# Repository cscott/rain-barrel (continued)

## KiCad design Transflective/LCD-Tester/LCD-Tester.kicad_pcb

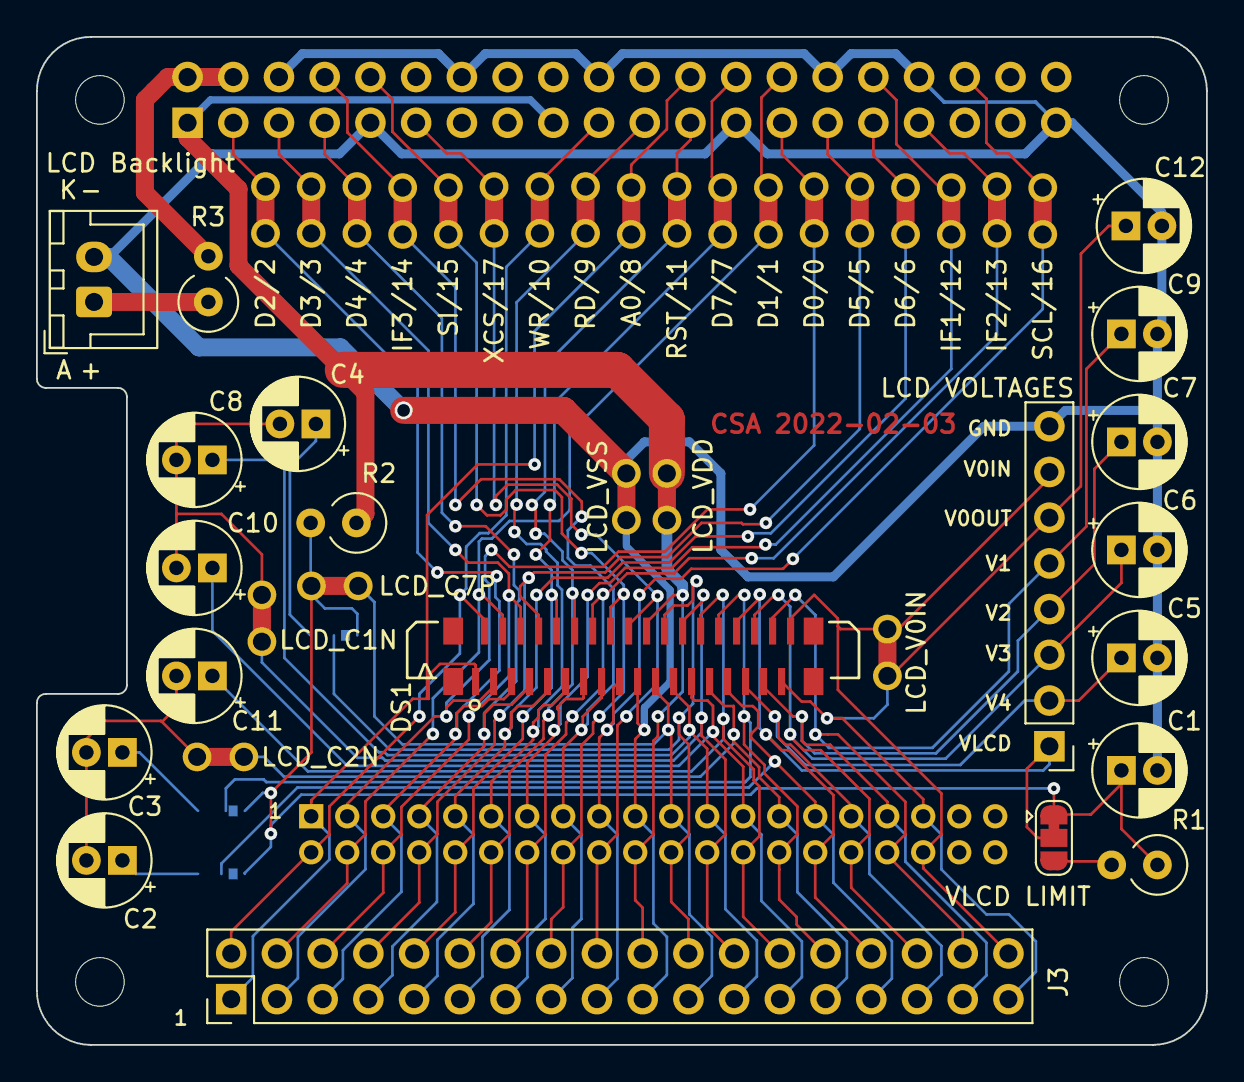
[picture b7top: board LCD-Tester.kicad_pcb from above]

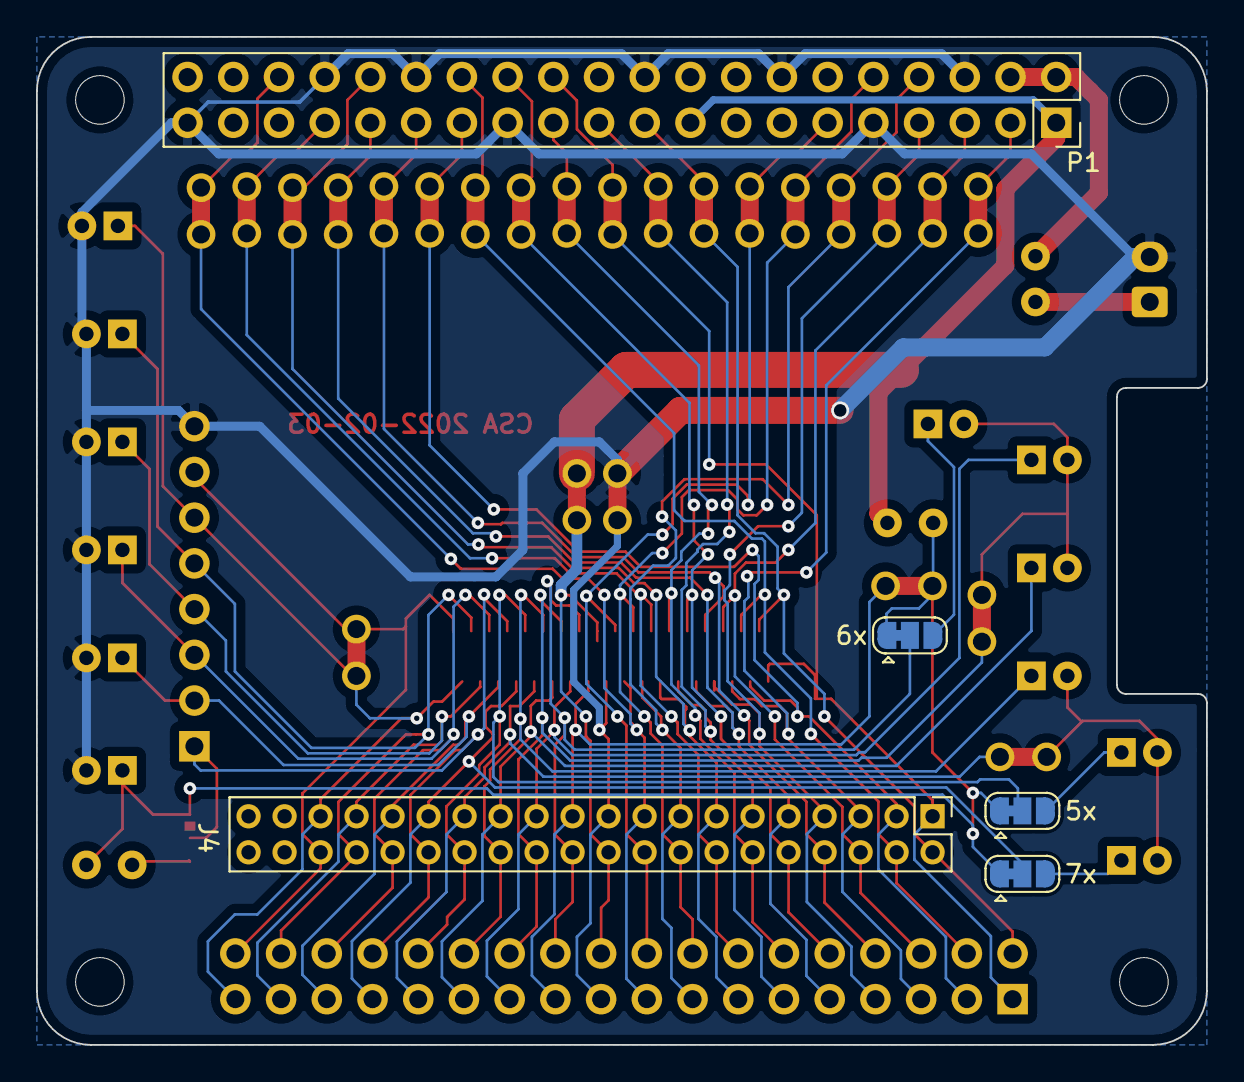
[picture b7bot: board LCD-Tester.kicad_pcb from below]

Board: 2 copper layers, 65.0 x 56.0 mm, 53 parts (5 on the bottom side), 65 nets.

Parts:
C1, C2, C3, C4, C5, C6, C7, C8, C9, C10, C11, C12: 1uF; CP_Radial_D5.0mm_P2.00mm
DS1: DISPLAYTECH-128240D; F314-1A7H1-11036
J1: LCD VOLTAGES; PinHeader_1x08_P2.54mm_Vertical
J2: LCD Backlight; JST_XH_B2B-XH-A_1x02_P2.50mm_Vertical
J3: Conn_01x36_Male; PinHeader_2x18_P2.54mm_Vertical
J4: Conn_01x36_Male; PinHeader_2x20_P2.00mm_Vertical
JP1: D2/2; Jumper-THT-NC
JP2: D3/3; Jumper-THT-NC
JP3: D4/4; Jumper-THT-NC
JP4: XCS/17; Jumper-THT-NC
JP5: WR/10; Jumper-THT-NC
JP6: RD/9; Jumper-THT-NC
JP7: RST/11; Jumper-THT-NC
JP8: D0/0; Jumper-THT-NC
JP9: D5/5; Jumper-THT-NC
JP10: D6/6; Jumper-THT-NC
JP11: IF2/13; Jumper-THT-NC
JP12: IF3/14; Jumper-THT-NC
JP13: SI/15; Jumper-THT-NC
JP14: A0/8; Jumper-THT-NC
JP15: D7/7; Jumper-THT-NC
JP16: D1/1; Jumper-THT-NC
JP17: IF1/12; Jumper-THT-NC
JP18: SCL/16; Jumper-THT-NC
JP19: VLCD LIMIT; SolderJumper-3_P1.3mm_Bridged12_RoundedPad1.0x1.5mm
JP20: 7x; SolderJumper-3_P1.3mm_Bridged12_RoundedPad1.0x1.5mm
JP21: 5x; SolderJumper-3_P1.3mm_Bridged12_RoundedPad1.0x1.5mm
JP22: 6x; SolderJumper-3_P1.3mm_Bridged12_RoundedPad1.0x1.5mm
JP23: LCD_V0IN; Jumper-THT-NC
JP24: LCD_C7P; Jumper-THT-NC
JP25: LCD_C1N; Jumper-THT-NC
JP26: LCD_C2N; Jumper-THT-NC
JP27: LCD_VDD; Jumper-THT-NC
JP28: LCD_VSS; Jumper-THT-NC
MK1, MK2, MK3, MK4: M2.5; MountingHole_2.7mm_M2.5
P1: Conn_02x20_Odd_Even; PinSocket_2x20_P2.54mm_Vertical
R1: 200; R_Axial_DIN0309_L9.0mm_D3.2mm_P2.54mm_Vertical
R2: 1M; R_Axial_DIN0309_L9.0mm_D3.2mm_P2.54mm_Vertical
R3: 15; R_Axial_DIN0309_L9.0mm_D3.2mm_P2.54mm_Vertical

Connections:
+3V3: JP27.1, P1.1, P1.17, R2.1
+5V: P1.2, P1.4, R3.2
/GPIO0: JP8.2, P1.27
/GPIO1: JP16.1, P1.28
/GPIO2: JP1.2, P1.3
/GPIO3: JP2.2, P1.5
/GPIO4: JP3.2, P1.7
/GPIO5: JP9.2, P1.29
/GPIO6: JP10.2, P1.31
/GPIO7: JP15.1, P1.26
/GPIO8: JP14.1, P1.24
/GPIO9: JP6.2, P1.21
/GPIO10: JP5.2, P1.19
/GPIO11: JP7.2, P1.23
/GPIO12: JP17.1, P1.32
/GPIO13: JP11.2, P1.33
/GPIO14: JP12.1, P1.8
/GPIO15: JP13.1, P1.10
/GPIO16: JP18.1, P1.36
/GPIO17: JP4.2, P1.11
/LCD_A0: DS1.1, J3.1, J4.1, JP14.2
/LCD_BACKLIGHT_A: J2.1, R3.1
/LCD_C1N: DS1.24, J3.24, J4.24, JP25.2
/LCD_C1P: C10.1, DS1.25, J3.25, J4.25
/LCD_C2N: DS1.27, J3.27, J4.27, JP26.2
/LCD_C2P: C11.1, DS1.26, J3.26, J4.26
/LCD_C3P: C8.1, DS1.23, J3.23, J4.23
/LCD_C4P: DS1.28, J3.28, J4.28, JP21.2
/LCD_C5P: DS1.22, J3.22, J4.22, JP22.2
/LCD_C6P: DS1.29, J3.29, J4.29, JP20.2
/LCD_C7P: DS1.21, J3.21, J4.21, JP24.2
/LCD_D0: DS1.3, J3.3, J4.3, JP8.1
/LCD_D1: DS1.4, J3.4, J4.4, JP16.2
/LCD_D2: DS1.5, J3.5, J4.5, JP1.1
/LCD_D3: DS1.6, J3.6, J4.6, JP2.1
/LCD_D4: DS1.7, J3.7, J4.7, JP3.1
/LCD_D5: DS1.8, J3.8, J4.8, JP9.1
/LCD_D6: DS1.9, J3.9, J4.9, JP10.1
/LCD_D7: DS1.10, J3.10, J4.10, JP15.2
/LCD_ERD: DS1.11, J3.11, J4.11, JP6.1
/LCD_IF1: DS1.13, J3.13, J4.13, JP17.2
/LCD_IF2: DS1.14, J3.14, J4.14, JP11.1
/LCD_IF3: DS1.15, J3.15, J4.15, JP12.2
/LCD_RST: DS1.12, J3.12, J4.12, JP7.1
/LCD_RWWR: DS1.2, J3.2, J4.2, JP5.1
/LCD_SCL: DS1.17, J3.17, J4.17, JP18.2
/LCD_SI: DS1.16, J3.16, J4.16, JP13.2
/LCD_V0IN: DS1.36, J1.7, J3.36, J4.36, JP23.2
/LCD_V0OUT: C12.1, DS1.35, J1.6, J3.35, J4.35, JP23.1
/LCD_V1: C9.1, DS1.34, J1.5, J3.34, J4.34
/LCD_V2: C7.1, DS1.33, J1.4, J3.33, J4.33
/LCD_V3: C6.1, DS1.32, J1.3, J3.32, J4.32
/LCD_V4: C5.1, DS1.31, J1.2, J3.31, J4.31
/LCD_VDD: DS1.20, J3.20, J4.20, JP27.2
/LCD_VLCD: DS1.30, J1.1, J3.30, J4.30, JP19.2
/LCD_VSS: DS1.19, J3.19, J4.19, JP28.2
/LCD_XCS: DS1.18, J3.18, J4.18, JP4.1
/VLCD: C1.1, JP19.1, JP20.1, JP21.1, JP22.1, JP24.1, R1.1, R2.2
GND: C1.2, C5.2, C6.2, C7.2, C9.2, C12.2, J1.8, J2.2, JP28.1, P1.6, P1.9, P1.14, P1.20, P1.25, P1.30, P1.34, P1.39
unnamed: C2.1, JP20.3
unnamed: C3.1, JP21.3
unnamed: C4.1, JP22.3
unnamed: C4.2, C8.2, C10.2, JP25.1
unnamed: C2.2, C3.2, C11.2, JP26.1
unnamed: JP19.3, R1.2

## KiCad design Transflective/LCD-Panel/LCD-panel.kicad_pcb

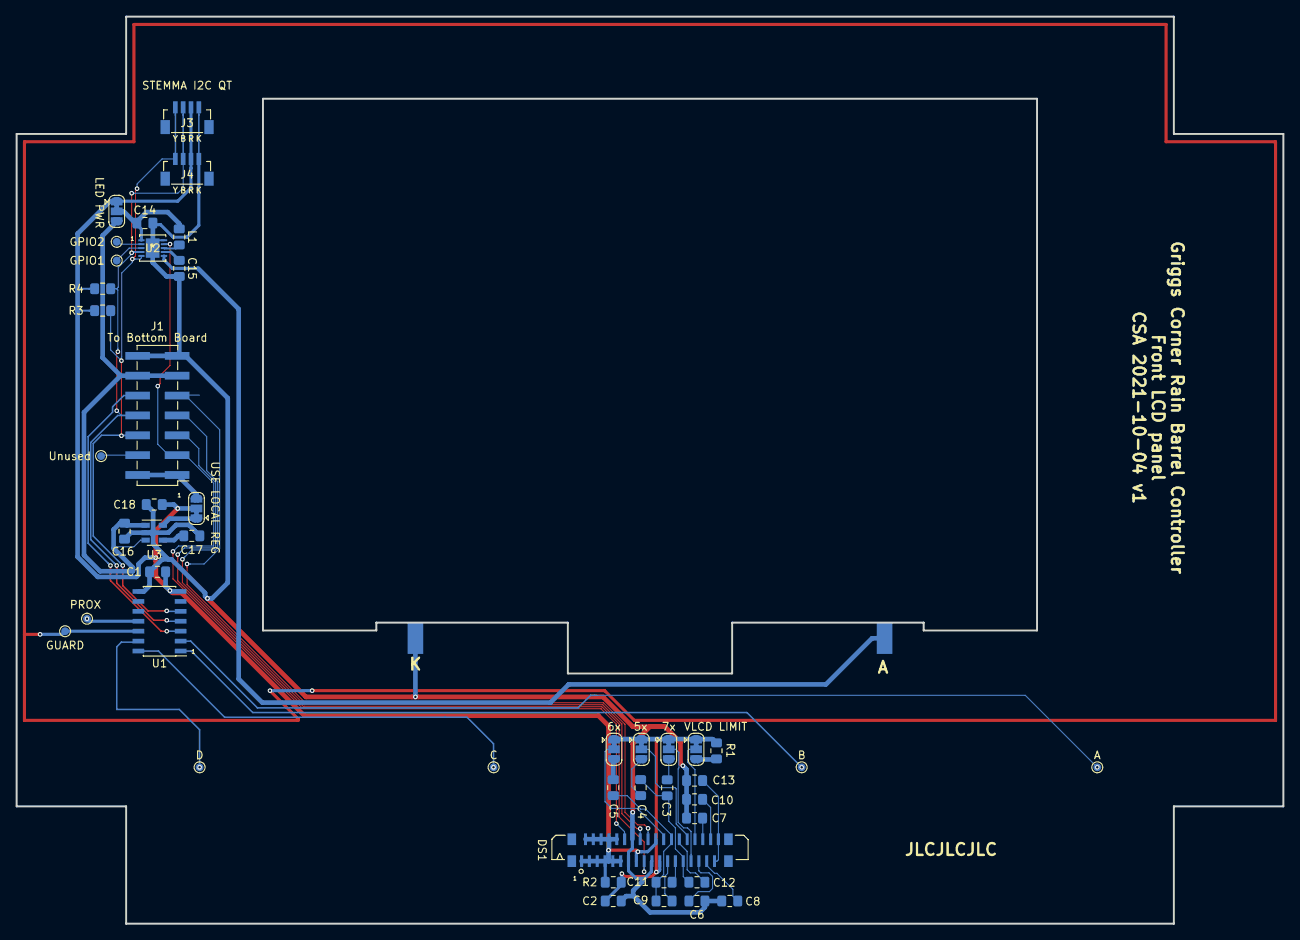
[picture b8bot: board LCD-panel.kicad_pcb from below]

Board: 2 copper layers, 162.0 x 116.0 mm, 46 parts (45 on the bottom side), 45 nets.

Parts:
C1, C16: .1uF; C_0805_2012Metric_Pad1.15x1.40mm_HandSolder
C2, C3, C4, C5, C6, C7, C8, C9, C10, C11, C12, C13, C18: 1uF; C_0805_2012Metric_Pad1.15x1.40mm_HandSolder
C14, C15: 10uF; C_0805_2012Metric_Pad1.15x1.40mm_HandSolder
C17: .01uF; C_0805_2012Metric_Pad1.15x1.40mm_HandSolder
DS1: DISPLAYTECH-128240D; F314-1A7H1-11036
J1: To Bottom Board; PinHeader_2x07_P2.54mm_Vertical_SMD
J2: DS BACKLIGHT; DisplayBacklight
J3, J4: STEMMA I2C QT; JST-SH-4-VERT-SMD
JP1: VLCD LIMIT; SolderJumper-3_P1.3mm_Bridged12_RoundedPad1.0x1.5mm
JP2: 7x; SolderJumper-3_P1.3mm_Bridged12_RoundedPad1.0x1.5mm
JP3: 5x; SolderJumper-3_P1.3mm_Bridged12_RoundedPad1.0x1.5mm
JP4: 6x; SolderJumper-3_P1.3mm_Bridged12_RoundedPad1.0x1.5mm
JP5: LED PWR; SolderJumper-3_P1.3mm_Bridged12_RoundedPad1.0x1.5mm
JP6: USE LOCAL REG; SolderJumper-3_P1.3mm_Bridged12_RoundedPad1.0x1.5mm
L1: 1.0uH; L_0805_2012Metric_Pad1.15x1.40mm_HandSolder
R1: 200; R_0805_2012Metric_Pad1.15x1.40mm_HandSolder
R2: 1M; R_0805_2012Metric_Pad1.15x1.40mm_HandSolder
R3, R4: 10k; R_0805_2012Metric_Pad1.15x1.40mm_HandSolder
TP1: GUARD; TestPoint_Pad_D1.0mm
TP2: A; TestPoint_Pad_D1.0mm
TP3: B; TestPoint_Pad_D1.0mm
TP4: C; TestPoint_Pad_D1.0mm
TP5: D; TestPoint_Pad_D1.0mm
TP6: PROX; TestPoint_Pad_D1.0mm
TP7: GPIO1; TestPoint_Pad_D1.0mm
TP8: GPIO2; TestPoint_Pad_D1.0mm
TP9: Unused; TestPoint_Pad_D1.0mm
U1: CAP1298; SOIC-14_3.9x8.7mm_P1.27mm
U2: ADP1650ACPZ-R7
U3: AP131-33; SOT-23-5

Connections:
+3V3: C1.1, C18.1, DS1.1, DS1.2, DS1.3, DS1.4, DS1.5, DS1.6, DS1.7, DS1.8, DS1.9, DS1.10, DS1.11, DS1.15, DS1.20, J3.2, J4.2, JP5.1, JP6.2, R2.1, R3.1, R4.1, U1.7
+5V: C16.1, J1.11, J1.12, JP5.3, U3.1, U3.3
/BUTTON_A: TP2.1, U1.2
/BUTTON_B: TP3.1, U1.1
/BUTTON_C: TP4.1, U1.14
/BUTTON_D: TP5.1, U1.13
/BUTTON_PROX: TP6.1, U1.11
/CAP_ALERT: J1.10, U1.3
/CAP_CLK: J1.6, J3.4, J4.4, R3.2, U1.5, U2.5
/CAP_DAT: J1.8, J3.3, J4.3, R4.2, U1.4, U2.4
/CAP_GUARD: TP1.1, U1.12
/DS_A: J2.A, U2.6
/DS_CLK: DS1.17, J1.5
/DS_CS: DS1.18, J1.9
/DS_DAT: DS1.16, J1.7
/DS_RST: DS1.12, J1.3, U2.9
/VLCD: C2.1, DS1.21, JP1.1, JP2.1, JP3.1, JP4.1, R1.1, R2.2
GND: C1.2, C2.2, C6.2, C7.2, C8.2, C10.2, C13.2, C14.2, C15.2, C16.2, C17.2, C18.2, DS1.13, DS1.14, DS1.19, J1.13, J1.14, J2.K, J3.1, J4.1, U1.8, U2.10, U2.11, U3.2
unnamed: C3.1, JP2.3
unnamed: C4.1, JP3.3
unnamed: C5.1, JP4.3
unnamed: C6.1, DS1.31
unnamed: C7.1, DS1.32
unnamed: C8.1, DS1.33
unnamed: C9.1, DS1.23
unnamed: C10.1, DS1.34
unnamed: C11.1, DS1.25
unnamed: C5.2, C9.2, C11.2, DS1.24
unnamed: C12.1, DS1.26
unnamed: C3.2, C4.2, C12.2, DS1.27
unnamed: C13.1, DS1.35, DS1.36
unnamed: C14.1, JP5.2, L1.1, U2.1
unnamed: C15.1, U2.7
unnamed: C17.1, U3.4
unnamed: DS1.22, JP4.2
unnamed: DS1.28, JP3.2
unnamed: DS1.29, JP2.2
unnamed: DS1.30, JP1.2
unnamed: J1.1, J1.2, JP6.3
unnamed: J1.4, TP9.1
unnamed: JP1.3, R1.2
unnamed: JP6.1, U3.5
unnamed: L1.2, U2.8
unnamed: TP7.1, U2.3
unnamed: TP8.1, U2.2

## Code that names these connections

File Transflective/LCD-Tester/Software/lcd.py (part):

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USE_CS = True

# set up pins
LCD_D2=2
LCD_D3=3
LCD_D4=4
LCD_XCS=17
LCD_RWWR=10
LCD_ERD=9
LCD_RST=11
LCD_D0=0
LCD_D5=5
LCD_D6=6
LCD_IF2=13
LCD_IF3=14
LCD_SI=15
LCD_A0=8
LCD_D7=7
LCD_D1=1
LCD_IF1=12
LCD_SCL=16
LCD_DATA=[LCD_D0, LCD_D1, LCD_D2, LCD_D3, LCD_D4, LCD_D5, LCD_D6, LCD_D7]
# set up data bus, initially as Hi-Z
def init():
    GPIO.setmode(GPIO.BCM) # pin numbers on rasp pi header
    GPIO.setup(LCD_RST, GPIO.OUT, initial=GPIO.LOW)
    for pin in LCD_DATA:
        GPIO.setup(pin, GPIO.IN)
    # set up output pins
    # 68-series 8-bit parallel, or 9-bit SPI mode
    GPIO.setup(LCD_IF1, GPIO.OUT, initial=GPIO.LOW)
    GPIO.setup(LCD_IF2, GPIO.OUT, initial=GPIO.HIGH if PARALLEL else GPIO.LOW)
    GPIO.setup(LCD_IF3, GPIO.OUT, initial=GPIO.HIGH)
    GPIO.setup(LCD_A0, GPIO.OUT, initial=GPIO.LOW)
    GPIO.setup(LCD_RWWR, GPIO.OUT, initial=GPIO.HIGH)
    GPIO.setup(LCD_ERD, GPIO.OUT, initial=GPIO.HIGH)
    GPIO.setup(LCD_SI, GPIO.OUT, initial=GPIO.LOW)
    GPIO.setup(LCD_SCL, GPIO.OUT, initial=GPIO.LOW)
    GPIO.setup(LCD_XCS, GPIO.OUT, initial=GPIO.HIGH if USE_CS else GPIO.LOW)

    reset()

def write_serial(a0, val):
    GPIO.output(LCD_SCL, 1)
    if USE_CS: GPIO.output(LCD_XCS, 0)
    GPIO.output(LCD_SI, a0)
    GPIO.output(LCD_SCL, 0)
    GPIO.output(LCD_SCL, 1) # latch at rising edge
    for bit in range(8):
        GPIO.output(LCD_SCL, 0)
        GPIO.output(LCD_SI, val&0x80) # MSB first
        val = val << 1
        GPIO.output(LCD_SCL, 1) # latch at rising edge
    if USE_CS: GPIO.output(LCD_XCS, 1)

def write_parallel(a0, val):
    GPIO.output(LCD_A0, a0)
    GPIO.output(LCD_RWWR, 0)
    GPIO.output(LCD_ERD, 1)
    for pin in LCD_DATA:
        GPIO.setup(pin, GPIO.OUT, initial=(val&1))
        val = val >> 1
    GPIO.output(LCD_XCS, 0) # active low
    # data are latched at the falling edge of the E signal
    usleep(1)
    GPIO.output(LCD_ERD, 0)
    usleep(1) # actually 100ns
    GPIO.output(LCD_XCS, 1)
    GPIO.output(LCD_ERD, 1)
    for pin in LCD_DATA:
        GPIO.setup(pin, GPIO.IN)

def read_parallel(a0):
    GPIO.output(LCD_A0, a0)
    GPIO.output(LCD_RWWR, 1)
    GPIO.output(LCD_ERD, 1)
    GPIO.output(LCD_XCS, 0) # active low
    usleep(1) # 40ns
    val = 0
    for pin in reversed(LCD_DATA):
        val = val << 1
        if GPIO.input(pin): val = val | 0x1
    GPIO.output(LCD_XCS, 1)
    GPIO.output(LCD_ERD, 1)
    return val

def write_cmd(val):
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    # "Read register 1" -- this is PB1 of the VOLCTRL cmd
    write_cmd(0x7C)
    low = read_cmd()
    # "Read register 2" -- this is PB2 of the VOLCTRL cmd
    write_cmd(0x7D)
    high = read_cmd()
    both = (low&0x3F) | (high<<6)
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
def reset():
    # in 68-series 8-bit parallel mode
    GPIO.output(LCD_RST, GPIO.LOW)
    usleep(1)
    GPIO.output(LCD_RST, GPIO.HIGH)
    usleep(2)
    write_cmd(0x0025) # NOP
    write_cmd(0x0025) # NOP
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
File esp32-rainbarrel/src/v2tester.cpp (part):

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#define BLACK SH110X_BLACK

// OLED FeatherWing buttons map to different pins depending on board:
#define BUTTON_A  0
#define BUTTON_B 16
#define BUTTON_C  2
#endif

// Other config
#ifdef V2TESTER
# define LED_GPIO        0
# define LCD_RST         2      // F0
# define PRESSURE_SW_IN 16      // F1 (pressure switch input)
# define PUMP_CNTRL      0      // F2 (power tail out)
# define LCD_CS         15      // F3
# define WATER_SENSE    12      // F5 (water present) (also MISO)
# define LCD_SI         13 // MOSI
# define LCD_SCL        14 // SCK
#endif
#ifdef V2TESTER32
# define LED_GPIO       13
# define LCD_RST        14      // F0
# define PRESSURE_SW_IN 32      // F1 (pressure switch input)
# define PUMP_CNTRL     15      // F2 (power tail out)
# define LCD_CS         33      // F3
# define WATER_SENSE    12      // F5 (water present, has a pull-down, boot!)
# define LCD_SI         18 // MOSI
# define LCD_SCL         5 // SCK
#endif

#define LED_OFF 1 // active low
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  digitalWrite(LCD_CS, 1);
  pinMode(LCD_CS, OUTPUT);
  digitalWrite(LCD_RST, 0);
  pinMode(LCD_RST, OUTPUT);

  adp1650_found = false;
  uint8_t val;
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#ifdef HAS_OLED
  // OLED setup
  display.begin(0x3C, true); // Address 0x3C default
  pinMode(BUTTON_A, INPUT_PULLUP);
  pinMode(BUTTON_B, INPUT_PULLUP);
  pinMode(BUTTON_C, INPUT_PULLUP);
#endif
#ifdef HAS_ST7529
  // assume that if adp1650 was found, then external booster is being used
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
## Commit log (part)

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2021-06-01 Initial commit of working version of esp32 rainpump server
2021-06-01 Use StaticJsonDocument
2021-06-02 Hook up to an Adafruit IO feed!
2021-06-02 Move files into src directory
2021-06-02 Convert to platformio
2021-06-02 Move header files to include/
2021-06-02 Add some links to the README
2021-06-03 Add capacitive touch
    Unfortunately there seems to be a bug with the magtag hardware here.
    I2C device 0x5A is found, but the initialization fails. :(
2021-06-03 Fritzing schematic for water level sensor amps
2021-06-03 Switch to alternate MPR121 driver for capacitive touch
    This version is hacky, but it actually works on the MagTag
2021-06-03 Add active rectifier to level amps to protect against negative inputs
    Ensure that if/when the water level sensor is disconnected, or for
    some reason the zero level drops below 4mA, that we don't subject
    the ESP32-S2 to a negative input pin level.
2021-06-17 Read levels from ESP32-S2 A/D converter, which is quite noisy (alas)
2021-06-17 Tweaks to LevelAmps (I've forgetten exactly what changed, sorry)
2021-06-17 Tweaks to rain gauge (show buttons presses, scale barrel levels, etc)
2021-06-17 Slight improvements to rain pump main web page information
2021-06-17 Use IP instead of local hostname for upload
    The mDNS appears to stop working after some period of time, while the
    IP-based uploading keeps working fine. Hmm.
2021-06-18 Improve capacitive touch sensing
    Bug fixes from the MPR121 datasheet
2021-06-18 Clean up button press / audio handling
2021-06-18 Increase bandwidth of rain gauge
2021-06-18 Add flowmeter source skeleton
2021-06-18 Use "I2C Sender" example
    From https://www.arduino.cc/en/Tutorial/LibraryExamples/MasterReader
2021-06-18 Add target for flowtester based on Feather Huzzah board with OLED display
2021-06-18 Make flowtester functional!
2021-06-18 Ensure rain gauge filter bandwidth isn't thrown off by a display refresh
2021-06-18 Lengthen debounce interval of flowmeter by a smidge
2021-06-22 The buttons on rainpump got wet, so temporarily disable them
2021-06-22 Link to adafruit dashboard, renormalize "water full" level
2021-06-22 Draft code to read flow meter
2021-06-22 Refactor platformio.ini to put common declarations at the top
2021-06-22 Skeleton to build a raspberry pi pico program for the SMRT-Y snitch
2021-06-23 rainpump: re-enable buttons, adjust max level, less smoothing, enable flowmeter
2021-06-23 rainpump: Suppress zeroes from flowmeter
2021-07-06 Circuits for the SMRT-Y snitch
    First simple version had trouble maintaining the virtual ground.
    It was likely a combination of three things: a wiring error that
    connected somethings to the "real" ground not the "virtual ground",
    overly-large resistors in the reference voltage divider (TL084 has
    input impedance which is significant in this case), and the TL084
    misbehaving when run as a comparator (it doesn't like its outputs
2021-07-07 I2C client code for the SMRT-Y snitch
2021-07-07 Use the PIO to blink the LED!
    There's no proper pioasm support in platformio (yet!) but we can
    manually compile our pio files here: https://wokwi.com/tools/pioasm
2021-07-07 Add testing infrastructure
2021-07-07 First version of SMRT-Y snitch PIO program to capture timer values on edges
2021-07-08 Improve PIO program to have 3 system clock cycle resolution
2021-07-08 smrtysnitch: First attempt at hooking everything up!
2021-07-08 Improvements to the SNITCH_TESTER (nee flowtester)
2021-07-09 snitch: add more testing data, improve algo to handle asym hi/low pulses
    Since our comparator and our phototransistor are both pull-down only,
    the resulting pulses tend to be asymmetric: the rise time is much longer
    than the fall time. DC bias will also cause this. Compensate by allowing
    shorter and longer pulses, but only if they balance out (ie a long pulse
    must be followed by a short one, and vice versa).
    Improve the test infrastructure and add a bunch of new tests to verify
2021-07-09 flowtester: Improve the display, explicitly init buffers
2021-07-09 snitch circuit: Component value tweaks for better performance.
2021-07-10 Improvements to the snitch I2C protocol (and to the flowtester)
2021-07-10 snitch: Ensure that pullups are disabled
2021-07-10 Convert arduino .ino to .cpp
2021-07-10 Add snitch support to rainpump
2021-07-10 More test data; widen the pulse criteria to allow for narrower pulses
2021-07-11 Add fritzing file for simple comparator circuit
    This uses a two-transistor differential amplifier setup.
2021-07-11 Rearrange breadboard to use fewer wires
2021-07-11 Dump raw decoded SMRTY values to an adafruit stream
    Don't know how to convert to %ages and degrees yet, but maybe I don't
    need to.
2021-07-11 SMRT-Y comparator: more breadboard tweaking
2021-07-11 More data!
2021-07-12 More test data; open up the pulse width thresholds
2021-07-12 Reduce pull-down on comparator to ensure we get below 0.8v logic low threshold
2021-07-12 rainpump/raingauge: Tweak intervals to be prime; slow down SMRT-Y updates
    Adjust all the millisecond intervals to be prime, so that the various timers
    tend to space themselves out over time instead of bunching up on 10s/60s
    boundaries.
    Also send only 2 updates/10s for the SMRT-Y monitor, to avoid throttling
    by adafruit IO. Previously we were generating 6 messages all in very
    short succession which was hitting the rate limiter.
2021-07-12 Some SMRT-Y decoding notes
2021-07-12 Initial decode of moisture % and soil temperature!
2021-07-13 Generate one flowmeter datapoint / day
2021-08-13 Update arduino framework to latest git
2021-08-13 New smrty-snitch optoisolator requires a pull up
2021-09-28 Start work on PCBs to use transflective screen and larger waterproof case
2021-09-28 Front panel functionally complete
    Still to do: verify orientation of LCD pinout, add 3.3V regulator option
2021-09-28 The FPC connector was mirrored :(
    Add a vertical FPC connector, with the proper orienatation. A bunch of
    stuff needs to be rerouted.
2021-09-28 Reroute the FPC connector
2021-10-04 Finish designing front and rear boards for Transflective LCD version
2021-10-17 Some notes about errata discovered in the v1 PCBs, and BOMs
2021-10-20 More PCB notes
2021-11-02 Add simple test program for the V2 "transflective" hardware
2021-11-03 Split snitchtester from flowtester; tweaks to v2tester; start lcdtester
2022-02-04 Gerbers off to JLCPCB for LCD tester board (raspberry pi hat)
2022-03-21 Uncommitted LCD tester software tweaks
2022-03-21 Export PDFs of schematics
2022-03-21 Notes from new LCD testing; raspberry pi software for tester board
2022-03-21 Update esp8266 lcd tester software: it works now!
2022-03-21 Only update the dirty window in the display
2022-03-21 Clean up the Adafruit GFX hack
2022-03-21 Copy esp32 rainpump/raingague code to v2rain.cpp
    Done as a standalone commit so that we can clearly see the changes
    made in the subsequent commit.
2022-03-21 Port raingauge to V2 hardware!
2022-03-21 Tweak reset delays to make LCD startup more reliable
2022-03-21 More work on v2 raingauge port
2022-03-21 Save memory by using a 2-bit-per-pixel framebuffer for the display
2022-03-21 Minor tweaks to v2 raingauge
2022-03-22 "Fixup" board for LCD panel, with fixed footprint for LED driver
    Also contains a step-up regulator to generate the LCD voltage of ~17V
    at low current.
2022-03-29 Tweaks to the v2tester program
2022-03-29 Port lcdtester to the Huzzah32 (ESP32)
2022-03-29 Port v2tester to the Huzzah32 (ESP32)
2022-03-30 Adjust display layout for the new 240x128px transflective display
2022-03-30 Hook up the ADC to the ESP32 rain gauge
2022-04-08 LCD fixup board: ADP1650 (with proper footprint), and external VLED supply
    Support these in the v2tester and the v2 rain gauge.
2022-10-20 Update pio to PlatformIO Core 6; remove old raingauge/rainpump targets
    The old version of the espressio sdk seems to be unsupported now in
    PIO 6; since we're not using that hardware anymore let's just remove it.
    (Commented it out for now because I might need some of the dependencies
    when I get the V2 rainpump working.)
2022-10-20 ST7529: get/set contrast support
2022-10-20 Add SNITCH GPIO feature
2022-10-20 Update rainpump to ESP32; remove support for 8266. Add config screen.
2022-10-24 Update Pico SMRTY snitch code to latest SDK, I2C assignments
    Switched to the earlphilhower SDK, not without some drama.
2022-10-24 Rain pump/gauge ESP32 updates
    * Fix mqtt reconnection logic
    * Add /test webserver endpoint for hardware testing; add more diagnostic
    information to main root webserver endpoint
    * Add some more diagnostic information to Config LCD screen on rain pump
    * Fix some pin configurations for the new V2 pump board
    * Don't allow infinite retry/hang on I2C error to the smrty snitch
2022-10-24 Clean up platformio.ini with build_src_filter
2022-10-24 snitch: Add embedded binary info, fix name of earle philhower port
2022-10-25 Swap CITY/RAIN valve GPIOs
2022-10-25 Make `#undef USE_MQTT` work again
2022-10-25 Bump up default contrast on raingauge display
2022-10-25 Add SECONDS_MS, MINUTES_MS, and HOURS_MS macros to make delays more readable
2022-10-25 Add daily flow feed
    Subscribes to Adafruit's hourly time service to stay sync'ed; does one
    update a day at the next hour after the first flow after reboot.
    Needed to fork Adafruit's MQTT library to allow non-blocking handling of
    subscription messages.
2023-05-30 Tweak LCD display
2023-06-20 Comments about unimplemented features / bugs
2023-06-20 Update w/ latest static IPs for rainpump/raingauge
2023-06-23 Remove unused MOTORSHIELD code
2023-06-23 Switch from Adafruit IO to Home Assistant logging
2023-06-27 New PCB for SMRT-Y snitch, skeleton template files
2023-07-04 New Turbine, Level Amp boards (2 versions), and SMRT-Y Snitch board
    Done with KiCAD 7; older designs migrated.
2023-07-10 Snitch PCB and BOM
2023-07-10 Level Chopper PCB, gerbers, BOM
2023-07-10 Turbine PCB, gerbers, BOM
2023-07-30 Remove old esp32-rainbarrel sources
2023-07-30 Document I2C addresses in use
2023-07-30 Fix bug w/ tried to update the pressure sensor from the raingauge
    Also improved the comment, to benefit future-me reading this.
2023-07-30 Add support for multiple flow meters
2023-07-30 Add export taken from the latest hardware; ignore all-zero SMRT-Y messages
2023-08-09 Give unique names to the different flowmeters
2023-08-09 Refactor the FOREACH macros a bit for flowmeters
2023-08-09 Allow a configurable number of rainbarrels
2023-08-09 Print all flowmeter readings on rainpump.local
2023-08-09 Use underscore before index uniformly for rain barrels and flow meters
2023-08-09 Allow a configurable number of snitches
2023-08-09 Add min/max controls for scaling each rain barrel
2023-08-12 HANumber needs a callback registered or it doesn't record the new value
2023-08-14 Minor improvements to the flowtester/snitchtester
2024-06-13 Add digispark fuse information
2024-06-13 3rd level sensor is now connected
2024-06-13 Change low water level to 5% (from 10%)
2024-06-13 Make water level low limit configurable via HA
2024-06-13 Improve SMRTY debug web page
2024-06-18 Set state class for HA binary sensors
2024-06-18 Add hysteresis to water alarm to prevent stuttering
2024-06-18 Ensure pump is off as early as possible in reboot
2024-06-18 Add bounce protection to pump switch
    Don't arc those contacts, it trips the AFCI.
2024-06-18 Different anti-bounce mechanism for pump
2024-06-18 Fixes to built-in webserver; update HA link
2025-11-08 Make contrast configurable
2025-11-08 Remove units of measurement from raingauge
    See
    https://github.com/home-assistant/core/issues/155785
2026-05-23 Update README.md and create an initial CLAUDE.md
    Created a docker "kit" for installing platformio into a docker sandbox.
2026-05-24 Reduce NUM_BARRELS to 2 in rainpump, and copy values across
    If only one barrel reports, use it as the value for both barrels, etc.
    This ensures that a malfunctioning sensor doesn't cause spurious
    empty/full readings; the remaining sensor values are used instead.
2026-05-24 Add delay after successful read to ensure adjacent sensors work
